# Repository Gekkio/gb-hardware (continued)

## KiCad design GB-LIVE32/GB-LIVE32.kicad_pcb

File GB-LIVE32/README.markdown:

# Notes

* Supports both PIC18F45K50 and PIC18LF45K50. If you use the LF version, you
  *must* populate the zero-ohm resistor to supply VUSB3V3. If you use the F
  version, you *must not* populate the zero-ohm resistor.
* All bus transceivers should be normal versions (without H in the part name.
  The GB CPU has pullups on data and address buses so they never float
  completely.
* The crude BAT54C-based power source switching probably draws power from the
  Game Boy even when USB is connected.
* Indicator LEDs use resistors with high values to minimize power consumption.
  If the LEDs don't work, use lower values (e.g. 1k).
* If soldering by hand, consider soldering the Molex 5-pin connector before the
  SRAM chip. They are a bit too close to each other and it's difficult to reach
  the Molex connector pins if the SRAM chip is already in place.
* Known USB spec violations:
  + The USB module should be turned on only when USB VBUS reaches a certain value.
  + USB suspend current is probably higher than the spec mandates.

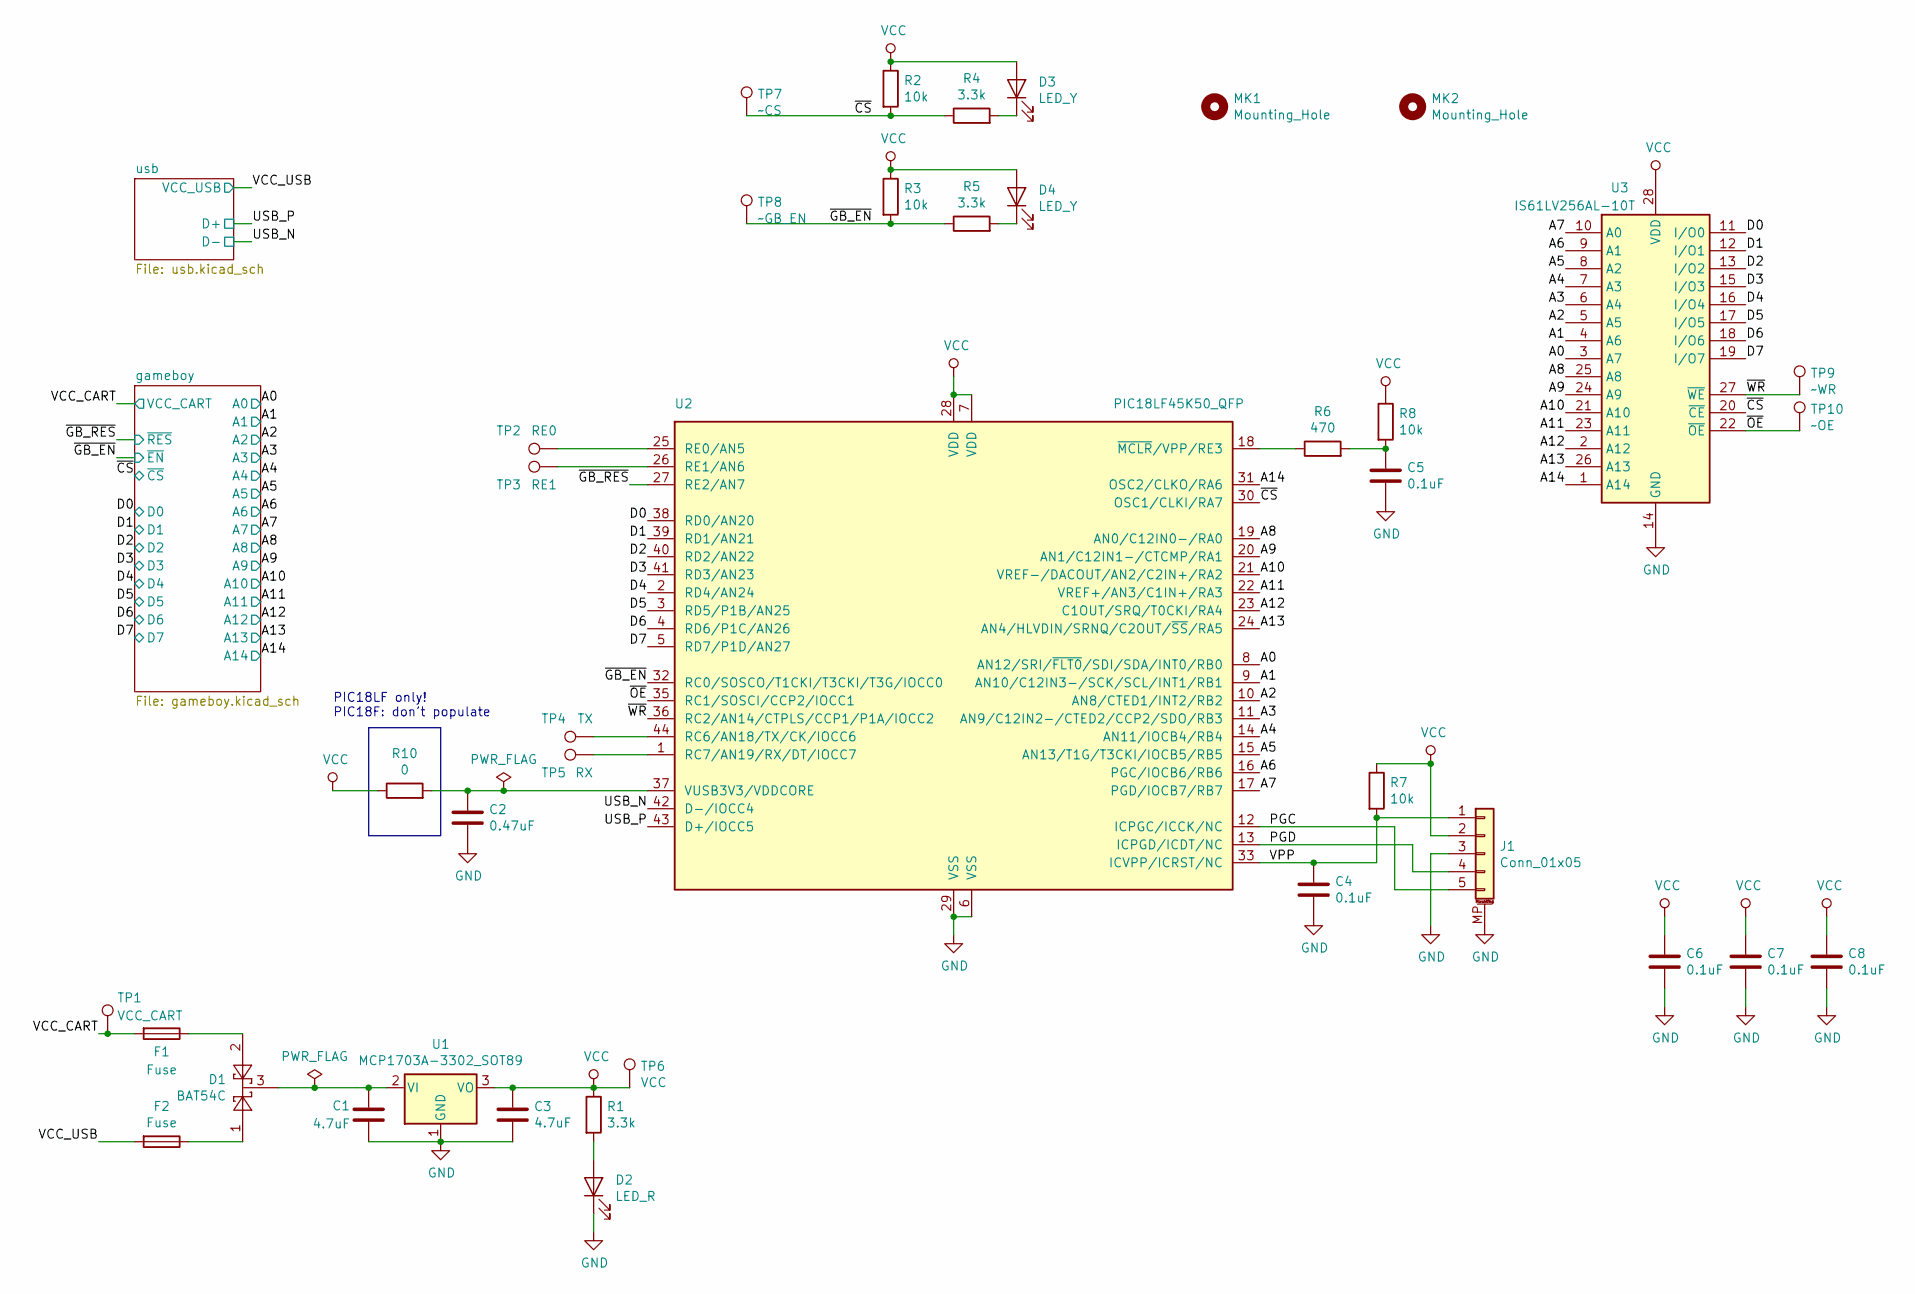
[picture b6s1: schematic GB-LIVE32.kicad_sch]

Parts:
C1, C3: 4.7uF; C_0805_2012Metric; Rating 16V X5R; MPN EMK212BJ475MD-T
C2: 0.47uF; C_0603_1608Metric; Rating 16V X5R; MPN C0603C474K4PACTU
C4, C5, C6, C7, C8: 0.1uF; C_0603_1608Metric; Rating 16V X5R; MPN C0603C104K3RECTU
D1: BAT54C; SOT-23; MPN BAT54CLT3G
D2: LED_R; LED_0603_1608Metric; MPN 150060SS75000
D3, D4: LED_Y; LED_0603_1608Metric; MPN 150060YS75000
F1, F2: Fuse; Fuse_0603_1608Metric; Rating 1.5A; MPN C2Q 1.5
J1: Conn_01x05; Molex_Pico-Lock_504050-0591_1x05-1MP_P1.50mm_Horizontal; MPN 504050-0591
MK1: Mounting_Hole; MountingHole_7.2mm
MK2: Mounting_Hole; MountingHole_2.3mm
R1, R4, R5: 3.3k; R_0603_1608Metric; Rating 1/10W 5%; MPN RC0603JR-133K3L
R2, R3, R7, R8: 10k; R_0603_1608Metric; Rating 1/10W 5%; MPN RC0603FR-0710KL
R6: 470; R_0603_1608Metric; Rating 1/10W 5%; MPN RC0603FR-10470RL
R10: 0; R_0603_1608Metric; Rating 1/10W 5%; MPN RC0603JR-070RL
TP1: VCC_CART; TestPoint_Pad_D1.0mm
TP2: RE0; TestPoint_Pad_D1.0mm
TP3: RE1; TestPoint_Pad_D1.0mm
TP4: TX; TestPoint_Pad_D1.0mm
TP5: RX; TestPoint_Pad_D1.0mm
TP6: VCC; TestPoint_Pad_D1.0mm
TP7: ~CS; TestPoint_Pad_D1.0mm
TP8: ~GB_EN; TestPoint_Pad_D1.0mm
TP9: ~WR; TestPoint_Pad_D1.0mm
TP10: ~OE; TestPoint_Pad_D1.0mm
U1: MCP1703A-3302_SOT89; SOT-89-3; MPN MCP1703T-3302E/MB
U2: PIC18LF45K50_QFP; TQFP-44_10x10mm_P0.8mm; MPN PIC18LF45K50-I/PT
U3: IS61LV256AL-10T; TSOP-I-28_11.8x8mm_P0.55mm_Pin1Middle; MPN IS61LV256AL-10TLI

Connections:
/A0: U2.8 (AN12/SRI/~FLT0/SDI/SDA/INT0/RB0), U3.3 (A7); also elsewhere on the board
/A1: U2.9 (AN10/C12IN3-/SCK/SCL/INT1/RB1), U3.4 (A6); also elsewhere on the board
/A2: U2.10 (AN8/CTED1/INT2/RB2), U3.5 (A5); also elsewhere on the board
/A3: U2.11 (AN9/C12IN2-/CTED2/CCP2/SDO/RB3), U3.6 (A4); also elsewhere on the board
/A4: U2.14 (AN11/IOCB4/RB4), U3.7 (A3); also elsewhere on the board
/A5: U2.15 (AN13/T1G/T3CKI/IOCB5/RB5), U3.8 (A2); also elsewhere on the board
/A6: U2.16 (PGC/IOCB6/RB6), U3.9 (A1); also elsewhere on the board
/A7: U2.17 (PGD/IOCB7/RB7), U3.10 (A0); also elsewhere on the board
/A8: U2.19 (AN0/C12IN0-/RA0), U3.25 (A8); also elsewhere on the board
/A9: U2.20 (AN1/C12IN1-/CTCMP/RA1), U3.24 (A9); also elsewhere on the board
/A10: U2.21 (VREF-/DACOUT/AN2/C2IN+/RA2), U3.21 (A10); also elsewhere on the board
/A11: U2.22 (VREF+/AN3/C1IN+/RA3), U3.23 (A11); also elsewhere on the board
/A12: U2.23 (C1OUT/SRQ/T0CKI/RA4), U3.2 (A12); also elsewhere on the board
/A13: U2.24 (AN4/HLVDIN/SRNQ/C2OUT/~SS/RA5), U3.26 (A13); also elsewhere on the board
/A14: U2.31 (OSC2/CLKO/RA6), U3.1 (A14); also elsewhere on the board
/D0: U2.38 (RD0/AN20), U3.11 (I/O0); also elsewhere on the board
/D1: U2.39 (RD1/AN21), U3.12 (I/O1); also elsewhere on the board
/D2: U2.40 (RD2/AN22), U3.13 (I/O2); also elsewhere on the board
/D3: U2.41 (RD3/AN23), U3.15 (I/O3); also elsewhere on the board
/D4: U2.2 (RD4/AN24), U3.16 (I/O4); also elsewhere on the board
/D5: U2.3 (RD5/P1B/AN25), U3.17 (I/O5); also elsewhere on the board
/D6: U2.4 (RD6/P1C/AN26), U3.18 (I/O6); also elsewhere on the board
/D7: U2.5 (RD7/P1D/AN27), U3.19 (I/O7); also elsewhere on the board
/PGC: J1.5, U2.12 (ICPGC/ICCK/NC)
/PGD: J1.4, U2.13 (ICPGD/ICDT/NC)
/USB_N: U2.42 (D-/IOCC4); also elsewhere on the board
/USB_P: U2.43 (D+/IOCC5); also elsewhere on the board
/VCC_CART: F1.2, TP1.1; also elsewhere on the board
/VCC_USB: F2.2; also elsewhere on the board
/VPP: C4.2, J1.1, R7.2, U2.33 (ICVPP/ICRST/NC)
/~CS: R2.2, R4.1, TP7.1, U2.30 (OSC1/CLKI/RA7), U3.20 (~CE); also elsewhere on the board
/~GB_EN: R3.2, R5.1, TP8.1, U2.32 (RC0/SOSCO/T1CKI/T3CKI/T3G/IOCC0); also elsewhere on the board
/~GB_RES: U2.27 (RE2/AN7); also elsewhere on the board
/~OE: TP10.1, U2.35 (RC1/SOSCI/CCP2/IOCC1), U3.22 (~OE)
/~WR: TP9.1, U2.36 (RC2/AN14/CTPLS/CCP1/P1A/IOCC2), U3.27 (~WE)
GND: C1.1, C2.2, C3.1, C4.1, C5.1, C6.2, C7.2, C8.2, D2.1 (K), J1.3, J1.MP (MountPin), U1.1 (GND), U2.6 (VSS), U2.29 (VSS), U3.14 (GND); also elsewhere on the board
unnamed: C1.2, D1.3, U1.2 (VI)
unnamed: C2.1, R10.2, U2.37 (VUSB3V3/VDDCORE)
unnamed: C5.2, R6.2, R8.2
unnamed: D1.1, F2.1
unnamed: D1.2, F1.1
unnamed: D2.2 (A), R1.2
unnamed: D3.1 (K), R4.2
unnamed: D4.1 (K), R5.2
unnamed: R6.1, U2.18 (~MCLR/VPP/RE3)
unnamed: TP2.1, U2.25 (RE0/AN5)
unnamed: TP3.1, U2.26 (RE1/AN6)
unnamed: TP4.1, U2.44 (RC6/AN18/TX/CK/IOCC6)
unnamed: TP5.1, U2.1 (RC7/AN19/RX/DT/IOCC7)
VCC: C3.2, C6.1, C7.1, C8.1, D3.2 (A), D4.2 (A), J1.2, R1.1, R2.1, R3.1, R7.1, R8.1, R10.1, TP6.1, U1.3 (VO), U2.7 (VDD), U2.28 (VDD), U3.28 (VDD); also elsewhere on the board

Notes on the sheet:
PIC18LF only! PIC18F: don't populate

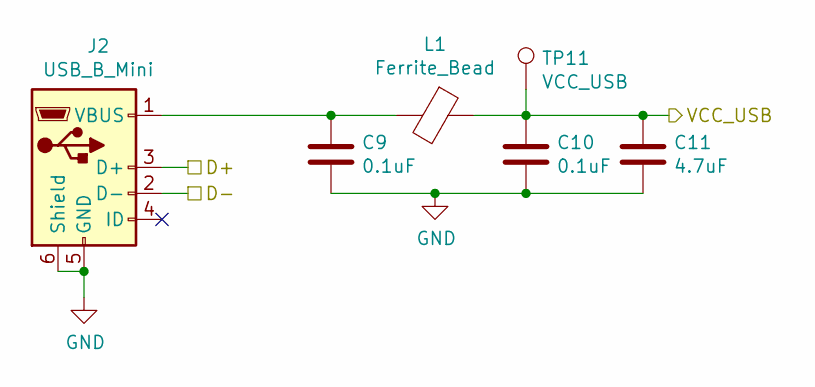
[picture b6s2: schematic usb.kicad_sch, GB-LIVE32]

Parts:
C9, C10: 0.1uF; C_0603_1608Metric; Rating 16V X5R; MPN C0603C104K3RECTU
C11: 4.7uF; C_0805_2012Metric; Rating 16V X5R; MPN EMK212BJ475MD-T
J2: USB_B_Mini; USB_Mini-B_Hirose_UX60SC-MB-5ST80_Horizontal; MPN UX60SC-MB-5ST(80)
L1: Ferrite_Bead; L_0603_1608Metric; MPN MMZ1608Y601BTD25
TP11: VCC_USB; TestPoint_Pad_D1.0mm

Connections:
/USB_N: J2.2 (D-); also elsewhere on the board
/USB_P: J2.3 (D+); also elsewhere on the board
/VCC_USB: C10.1, C11.2, L1.1, TP11.1; also elsewhere on the board
GND: C9.2, C10.2, C11.1, J2.5 (GND), J2.6 (Shield); also elsewhere on the board
unnamed: C9.1, J2.1 (VBUS), L1.2

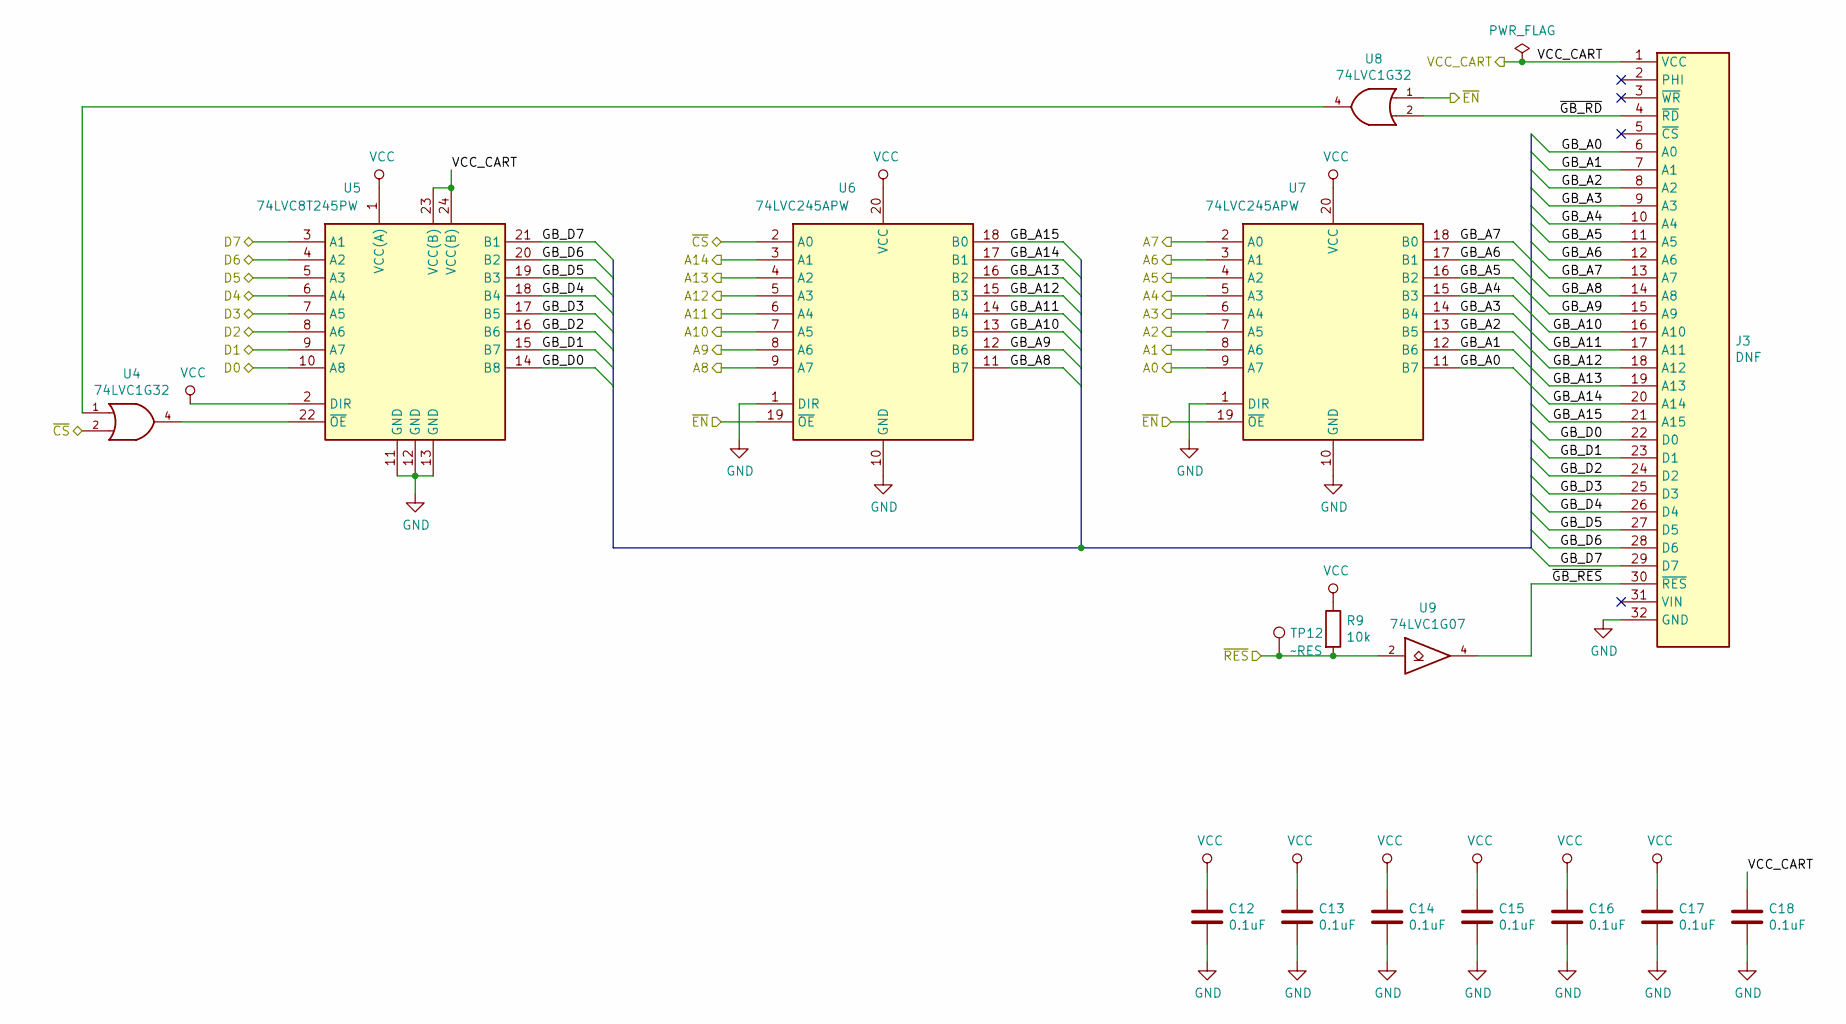
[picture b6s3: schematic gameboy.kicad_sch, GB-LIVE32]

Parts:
C12, C13, C14, C15, C16, C17, C18: 0.1uF; C_0603_1608Metric; Rating 16V X5R; MPN C0603C104K3RECTU
J3: DNF; GameBoy_Cartridge_1x32_P1.50mm_Edge
R9: 10k; R_0603_1608Metric; Rating 1/10W 5%; MPN RC0603FR-0710KL
TP12: ~RES; TestPoint_Pad_D1.0mm
U4, U8: 74LVC1G32; SOT-353_SC-70-5; MPN 74LVC1G32GW,125
U5: 74LVC8T245PW; TSSOP-24_4.4x7.8mm_P0.65mm; MPN 74LVC8T245PW,118
U6, U7: 74LVC245APW; TSSOP-20_4.4x6.5mm_P0.65mm; MPN 74LVC245APW,118
U9: 74LVC1G07; SOT-353_SC-70-5; MPN 74LVC1G07GW,125

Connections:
/A0: U7.9 (A7); also elsewhere on the board
/A1: U7.8 (A6); also elsewhere on the board
/A2: U7.7 (A5); also elsewhere on the board
/A3: U7.6 (A4); also elsewhere on the board
/A4: U7.5 (A3); also elsewhere on the board
/A5: U7.4 (A2); also elsewhere on the board
/A6: U7.3 (A1); also elsewhere on the board
/A7: U7.2 (A0); also elsewhere on the board
/A8: U6.9 (A7); also elsewhere on the board
/A9: U6.8 (A6); also elsewhere on the board
/A10: U6.7 (A5); also elsewhere on the board
/A11: U6.6 (A4); also elsewhere on the board
/A12: U6.5 (A3); also elsewhere on the board
/A13: U6.4 (A2); also elsewhere on the board
/A14: U6.3 (A1); also elsewhere on the board
/D0: U5.10 (A8); also elsewhere on the board
/D1: U5.9 (A7); also elsewhere on the board
/D2: U5.8 (A6); also elsewhere on the board
/D3: U5.7 (A5); also elsewhere on the board
/D4: U5.6 (A4); also elsewhere on the board
/D5: U5.5 (A3); also elsewhere on the board
/D6: U5.4 (A2); also elsewhere on the board
/D7: U5.3 (A1); also elsewhere on the board
/VCC_CART: C18.1, J3.1 (VCC), U5.23 (VCC(B)), U5.24 (VCC(B)); also elsewhere on the board
/gameboy/GB_A0: J3.6 (A0), U7.11 (B7)
/gameboy/GB_A1: J3.7 (A1), U7.12 (B6)
/gameboy/GB_A2: J3.8 (A2), U7.13 (B5)
/gameboy/GB_A3: J3.9 (A3), U7.14 (B4)
/gameboy/GB_A4: J3.10 (A4), U7.15 (B3)
/gameboy/GB_A5: J3.11 (A5), U7.16 (B2)
/gameboy/GB_A6: J3.12 (A6), U7.17 (B1)
/gameboy/GB_A7: J3.13 (A7), U7.18 (B0)
/gameboy/GB_A8: J3.14 (A8), U6.11 (B7)
/gameboy/GB_A9: J3.15 (A9), U6.12 (B6)
/gameboy/GB_A10: J3.16 (A10), U6.13 (B5)
/gameboy/GB_A11: J3.17 (A11), U6.14 (B4)
/gameboy/GB_A12: J3.18 (A12), U6.15 (B3)
/gameboy/GB_A13: J3.19 (A13), U6.16 (B2)
/gameboy/GB_A14: J3.20 (A14), U6.17 (B1)
/gameboy/GB_A15: J3.21 (A15), U6.18 (B0)
/gameboy/GB_D0: J3.22 (D0), U5.14 (B8)
/gameboy/GB_D1: J3.23 (D1), U5.15 (B7)
/gameboy/GB_D2: J3.24 (D2), U5.16 (B6)
/gameboy/GB_D3: J3.25 (D3), U5.17 (B5)
/gameboy/GB_D4: J3.26 (D4), U5.18 (B4)
/gameboy/GB_D5: J3.27 (D5), U5.19 (B3)
/gameboy/GB_D6: J3.28 (D6), U5.20 (B2)
/gameboy/GB_D7: J3.29 (D7), U5.21 (B1)
/gameboy/~GB_RD: J3.4 (~RD), U8.2
/gameboy/~GB_RES: J3.30 (~RES), U9.4
/~CS: U4.2, U6.2 (A0); also elsewhere on the board
/~GB_EN: U6.19 (~OE), U7.19 (~OE), U8.1; also elsewhere on the board
/~GB_RES: R9.2, TP12.1, U9.2; also elsewhere on the board
GND: C12.2, C13.2, C14.2, C15.2, C16.2, C17.2, C18.2, J3.32 (GND), U4.3 (GND), U5.11 (GND), U5.12 (GND), U5.13 (GND), U6.1 (DIR), U6.10 (GND), U7.1 (DIR), U7.10 (GND), U8.3 (GND), U9.3 (GND); also elsewhere on the board
unnamed: U4.1, U8.4
unnamed: U4.4, U5.22 (~OE)
VCC: C12.1, C13.1, C14.1, C15.1, C16.1, C17.1, R9.1, U4.5 (VCC), U5.1 (VCC(A)), U5.2 (DIR), U6.20 (VCC), U7.20 (VCC), U8.5 (VCC), U9.5 (VCC); also elsewhere on the board

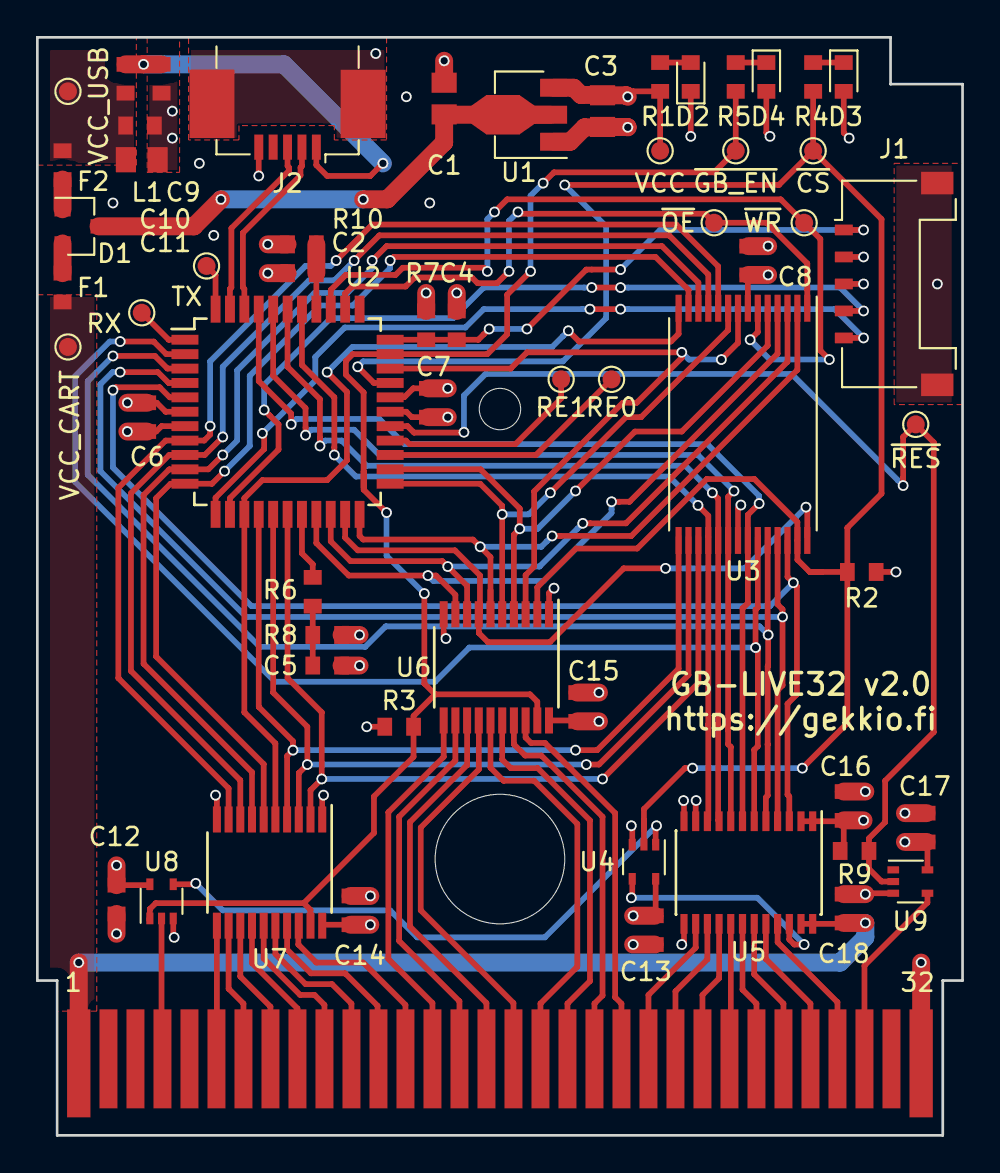
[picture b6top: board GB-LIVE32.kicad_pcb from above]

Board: 4 copper layers, 51.4 x 61.0 mm, 61 parts (0 on the bottom side), 79 nets.
